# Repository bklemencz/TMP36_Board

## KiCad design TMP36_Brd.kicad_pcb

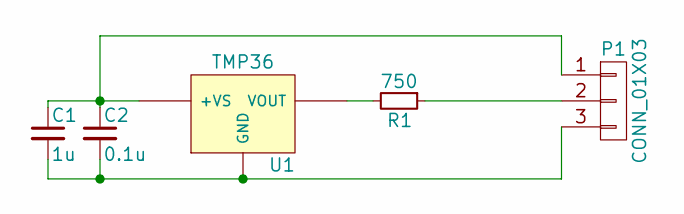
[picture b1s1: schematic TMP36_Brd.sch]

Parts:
C1: 1u; C_0805
C2: 0.1u; C_0805
P1: CONN_01X03; SolderPad_3pin
R1: 750; R_0805
U1: TMP36; TO-92_Horizontal2_Inline_Narrow_Oval

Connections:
unnamed: C1.1, C2.1, P1.1, U1.1 (+VS)
unnamed: C1.2, C2.2, P1.3, U1.3 (GND)
unnamed: P1.2, R1.1
unnamed: R1.2, U1.2 (VOUT)

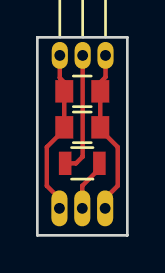
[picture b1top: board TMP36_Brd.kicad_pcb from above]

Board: 2 copper layers, 5.0 x 11.0 mm, 5 parts (0 on the bottom side), 4 nets.

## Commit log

2016-03-30 :lollipop: Added .gitattributes & .gitignore files
2016-03-30 Initial
